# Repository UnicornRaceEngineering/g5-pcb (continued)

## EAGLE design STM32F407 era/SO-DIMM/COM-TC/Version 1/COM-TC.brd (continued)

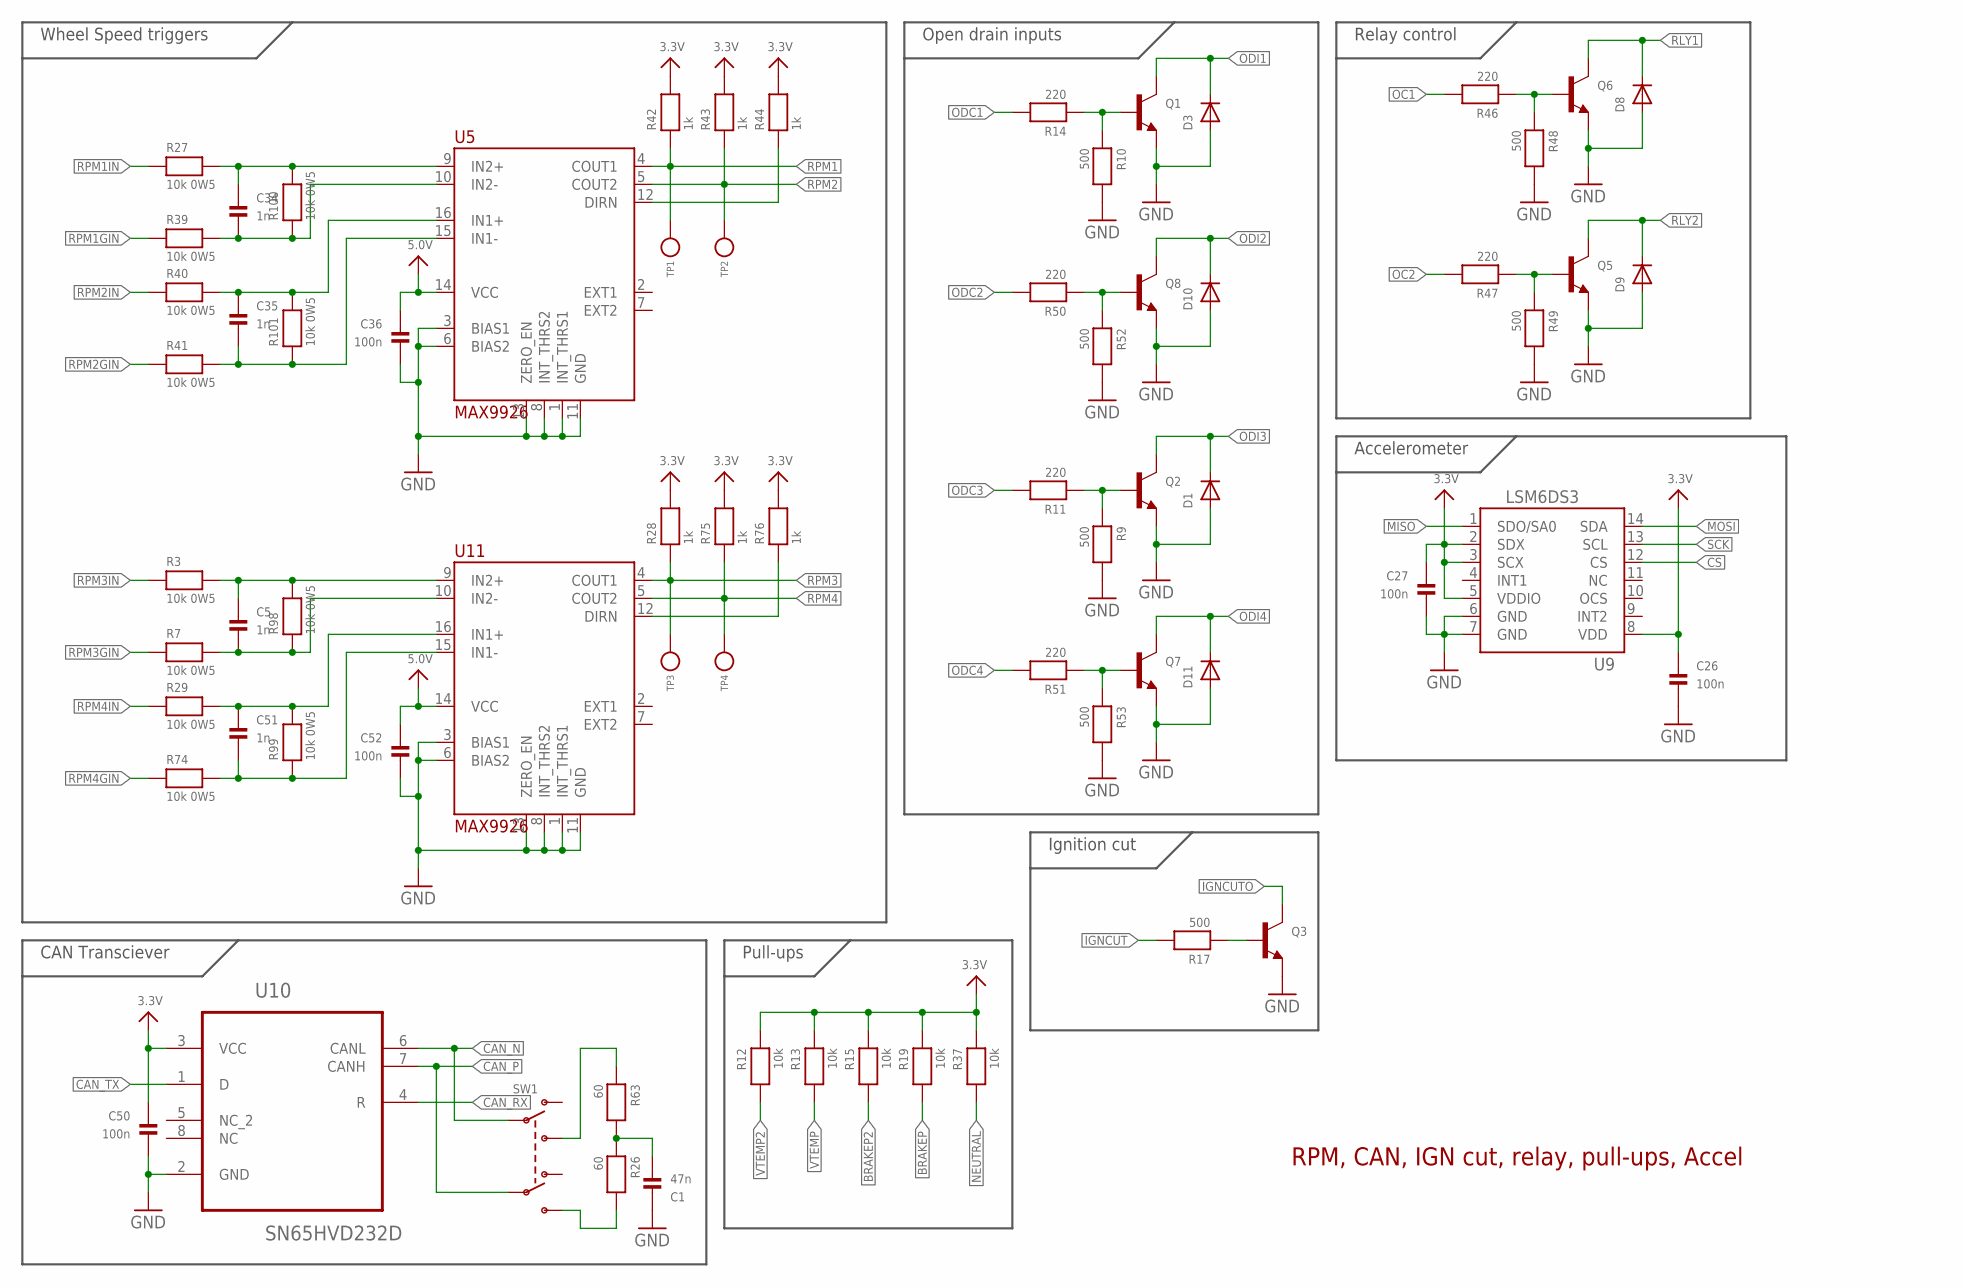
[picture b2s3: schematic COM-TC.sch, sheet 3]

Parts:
C1: 47n; _0603
C5, C34, C35, C51: 1n; _0603
C26, C27, C36, C50, C52: 100n; _0603
D1, D3, D8, D9, D10, D11: DIODESOD-323F; SOD-323F
Q1, Q2, Q3, Q5, Q6, Q7, Q8: TRANSISTOR_NPNWIDE; SOT23-WIDE
R3, R7, R27, R29, R39, R40, R41, R74, R98, R99, R100, R101: 10k 0W5; _0805
R9, R10, R17, R48, R49, R52, R53: 500; _0603
R11, R14, R46, R47, R50, R51: 220; _0603
R12, R13, R15, R19, R37: 10k; _0603
R26, R63: 60; _0603
R28, R42, R43, R44, R75, R76: 1k; _0603
SW1: SWITCH_DPDT; DPDT_SMT_JS202011SCQN
TP1, TP2, TP3, TP4: TEST_POINT_0.040IN; TESTPOINT_0.040IN
U5, U11: MAX9926; SOP63P600X175-16N
U9: LSM6DS3; LGA14L_DOT_INDICATOR
U10: SN65HVD232D; SOIC127P600X175-8N

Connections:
3.3V: C26.1, C27.1, C50.1, R12.1, R13.1, R15.1, R19.1, R28.2, R37.1, R42.2, R43.2, R44.2, R75.2, R76.2, U9.2 (SDX), U9.3 (SCX), U9.5 (VDDIO), U9.8 (VDD), U10.3 (VCC); also elsewhere on the board
5.0V: C36.1, C52.1, U5.14 (VCC), U11.14 (VCC); also elsewhere on the board
BRAKEP: R19.2; also elsewhere on the board
BRAKEP2: R15.2; also elsewhere on the board
CAN_N: SW1.P$2 (P1), U10.6 (CANL); also elsewhere on the board
CAN_P: SW1.P$5 (P2), U10.7 (CANH); also elsewhere on the board
CAN_RX: U10.4 (R); also elsewhere on the board
CAN_TX: U10.1 (D); also elsewhere on the board
CS: U9.12 (CS); also elsewhere on the board
GND: C1.1, C26.2, C27.2, C36.2, C50.2, C52.2, D1.A, D3.A, D8.A, D9.A, D10.A, D11.A, Q1.2 (E), Q2.2 (E), Q3.2 (E), Q5.2 (E), Q6.2 (E), Q7.2 (E), Q8.2 (E), R9.2, R10.2, R48.2, R49.2, R52.2, R53.2, U5.1 (INT_THRS1), U5.3 (BIAS1), U5.6 (BIAS2), U5.8 (INT_THRS2), U5.11 (GND), U5.13 (ZERO_EN), U9.6 (GND), U9.7 (GND), U10.2 (GND), U11.1 (INT_THRS1), U11.3 (BIAS1), U11.6 (BIAS2), U11.8 (INT_THRS2), U11.11 (GND), U11.13 (ZERO_EN); also elsewhere on the board
IGNCUT: R17.2; also elsewhere on the board
IGNCUTO: Q3.3 (C); also elsewhere on the board
MISO: U9.1 (SDO/SA0); also elsewhere on the board
MOSI: U9.14 (SDA); also elsewhere on the board
unnamed: R63.1, SW1.P$3 (S1)
unnamed: Q2.1 (B), R9.1, R11.1
unnamed: C1.2, R26.1, R63.2
unnamed: Q6.1 (B), R46.1, R48.1
unnamed: Q1.1 (B), R10.1, R14.1
unnamed: C34.1, R27.2, R100.2, U5.9 (IN2+)
unnamed: Q5.1 (B), R47.1, R49.1
unnamed: C35.2, R41.2, R101.1, U5.15 (IN1-)
unnamed: C5.1, R3.2, R98.2, U11.9 (IN2+)
unnamed: C35.1, R40.2, R101.2, U5.16 (IN1+)
unnamed: C34.2, R39.2, R100.1, U5.10 (IN2-)
unnamed: C51.2, R74.2, R99.1, U11.15 (IN1-)
unnamed: Q8.1 (B), R50.1, R52.1
unnamed: Q7.1 (B), R51.1, R53.1
unnamed: Q3.1 (B), R17.1
unnamed: C51.1, R29.2, R99.2, U11.16 (IN1+)
unnamed: C5.2, R7.2, R98.1, U11.10 (IN2-)
unnamed: R44.1, U5.12 (DIRN)
unnamed: R26.2, SW1.P$4 (S2)
unnamed: R76.1, U11.12 (DIRN)
NEUTRAL: R37.2; also elsewhere on the board
OC1: R46.2; also elsewhere on the board
OC2: R47.2; also elsewhere on the board
ODC1: R14.2; also elsewhere on the board
ODC2: R50.2; also elsewhere on the board
ODC3: R11.2; also elsewhere on the board
ODC4: R51.2; also elsewhere on the board
ODI1: D3.C, Q1.3 (C); also elsewhere on the board
ODI2: D10.C, Q8.3 (C); also elsewhere on the board
ODI3: D1.C, Q2.3 (C); also elsewhere on the board
ODI4: D11.C, Q7.3 (C); also elsewhere on the board
RLY1: D8.C, Q6.3 (C); also elsewhere on the board
RLY2: D9.C, Q5.3 (C); also elsewhere on the board
RPM1: R42.1, TP1.TESTPOINT, U5.4 (COUT1); also elsewhere on the board
RPM1GIN: R39.1; also elsewhere on the board
RPM1IN: R27.1; also elsewhere on the board
RPM2: R43.1, TP2.TESTPOINT, U5.5 (COUT2); also elsewhere on the board
RPM2GIN: R41.1; also elsewhere on the board
RPM2IN: R40.1; also elsewhere on the board
RPM3: R28.1, TP3.TESTPOINT, U11.4 (COUT1); also elsewhere on the board
RPM3GIN: R7.1; also elsewhere on the board
RPM3IN: R3.1; also elsewhere on the board
RPM4: R75.1, TP4.TESTPOINT, U11.5 (COUT2); also elsewhere on the board
RPM4GIN: R74.1; also elsewhere on the board
RPM4IN: R29.1; also elsewhere on the board
SCK: U9.13 (SCL); also elsewhere on the board
VTEMP: R13.2; also elsewhere on the board
VTEMP2: R12.2; also elsewhere on the board

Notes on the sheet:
CAN Transciever
Ignition cut
Wheel Speed triggers
Relay control
Open drain inputs
Pull-ups
Accelerometer
RPM, CAN, IGN cut, relay, pull-ups, Accel

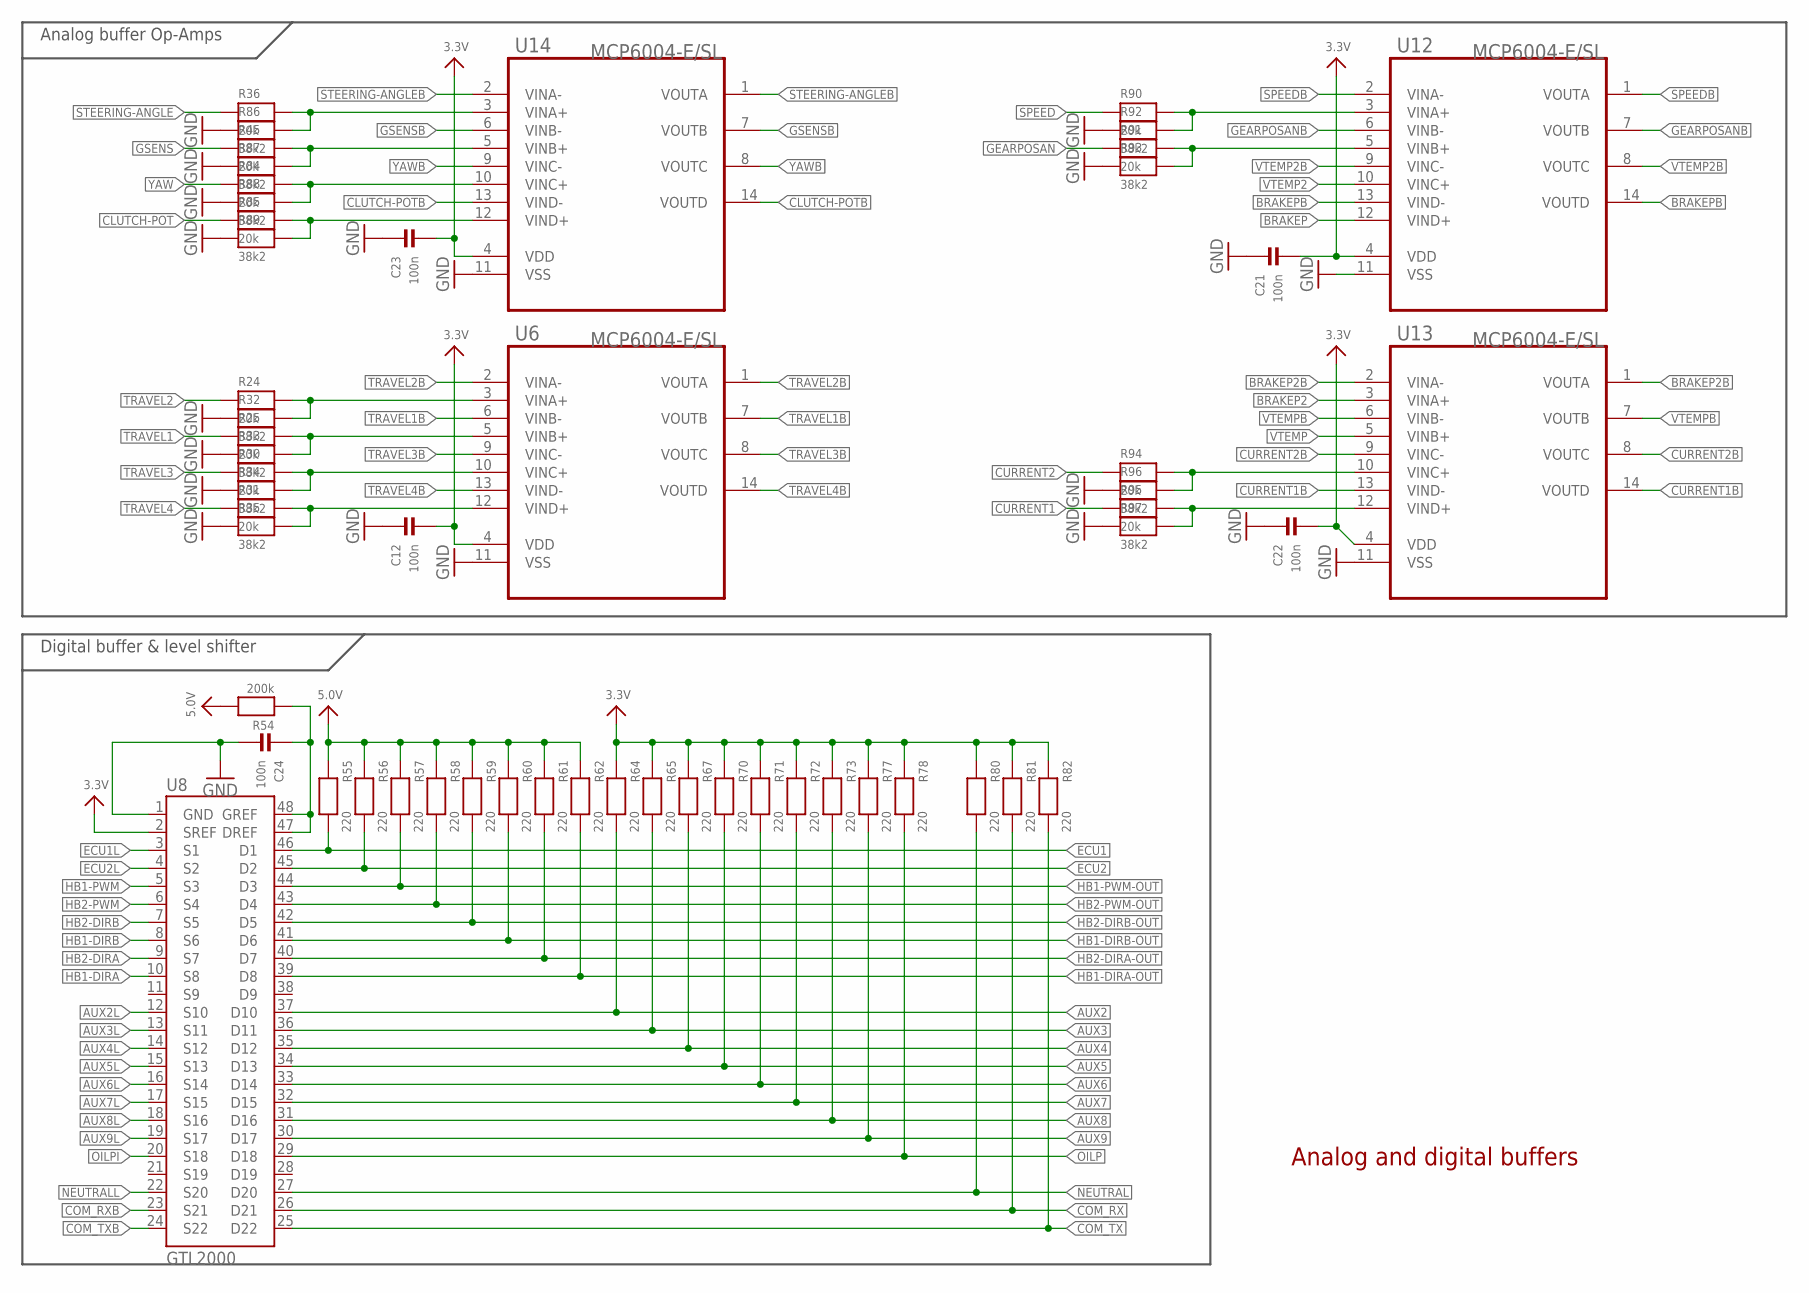
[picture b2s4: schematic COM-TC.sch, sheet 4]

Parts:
C12, C21, C22, C23, C24: 100n; _0603
R24, R25, R30, R31, R36, R45, R84, R85, R90, R91, R94, R95: 20k; _0603
R32, R33, R34, R35, R86, R87, R88, R89, R92, R93, R96, R97: 38k2; _0603
R54: 200k; _0603
R55, R56, R57, R58, R59, R60, R61, R62, R64, R65, R67, R70, R71, R72, R73, R77, R78, R80, R81, R82: 220; _0603
U6, U12, U13, U14: MCP6004-E/SL; SOIC127P600X175-14N
U8: GTL2000; TSSOP48

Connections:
3.3V: C12.2, C21.2, C22.2, C23.2, R64.1, R65.1, R67.1, R70.1, R71.1, R72.1, R73.1, R77.1, R78.1, R80.1, R81.1, R82.1, U6.4 (VDD), U8.2 (SREF), U12.4 (VDD), U13.4 (VDD), U14.4 (VDD); also elsewhere on the board
5.0V: R54.2, R55.1, R56.1, R57.1, R58.1, R59.1, R60.1, R61.1, R62.1; also elsewhere on the board
AUX2: R64.2, U8.37 (D10); also elsewhere on the board
AUX2L: U8.12 (S10); also elsewhere on the board
AUX3: R65.2, U8.36 (D11); also elsewhere on the board
AUX3L: U8.13 (S11); also elsewhere on the board
AUX4: R67.2, U8.35 (D12); also elsewhere on the board
AUX4L: U8.14 (S12); also elsewhere on the board
AUX5: R70.2, U8.34 (D13); also elsewhere on the board
AUX5L: U8.15 (S13); also elsewhere on the board
AUX6: R71.2, U8.33 (D14); also elsewhere on the board
AUX6L: U8.16 (S14); also elsewhere on the board
AUX7: R72.2, U8.32 (D15); also elsewhere on the board
AUX7L: U8.17 (S15); also elsewhere on the board
AUX8: R73.2, U8.31 (D16); also elsewhere on the board
AUX8L: U8.18 (S16); also elsewhere on the board
AUX9: R77.2, U8.30 (D17); also elsewhere on the board
AUX9L: U8.19 (S17); also elsewhere on the board
BRAKEP: U12.12 (VIND+); also elsewhere on the board
BRAKEP2: U13.3 (VINA+); also elsewhere on the board
BRAKEP2B: U13.1 (VOUTA), U13.2 (VINA-); also elsewhere on the board
BRAKEPB: U12.13 (VIND-), U12.14 (VOUTD); also elsewhere on the board
CLUTCH-POT: R85.1; also elsewhere on the board
CLUTCH-POT1: R31.2, R35.2, U6.12 (VIND+)
CLUTCH-POTB: U14.13 (VIND-), U14.14 (VOUTD); also elsewhere on the board
COM_RX: R81.2, U8.26 (D21); also elsewhere on the board
COM_RXB: U8.23 (S21); also elsewhere on the board
COM_TX: R82.2, U8.25 (D22); also elsewhere on the board
COM_TXB: U8.24 (S22); also elsewhere on the board
CURRENT1: R95.1; also elsewhere on the board
CURRENT1B: U13.13 (VIND-), U13.14 (VOUTD); also elsewhere on the board
CURRENT2: R94.1; also elsewhere on the board
CURRENT2B: U13.8 (VOUTC), U13.9 (VINC-); also elsewhere on the board
ECU1: R55.2, U8.46 (D1); also elsewhere on the board
ECU1L: U8.3 (S1); also elsewhere on the board
ECU2: R56.2, U8.45 (D2); also elsewhere on the board
ECU2L: U8.4 (S2); also elsewhere on the board
GEARPOSAN: R91.1; also elsewhere on the board
GEARPOSANB: U12.6 (VINB-), U12.7 (VOUTB); also elsewhere on the board
GND: C12.1, C21.1, C22.1, C23.1, C24.2, R32.1, R33.1, R34.1, R35.1, R86.1, R87.1, R88.1, R89.1, R92.1, R93.1, R96.1, R97.1, U6.11 (VSS), U8.1 (GND), U12.11 (VSS), U13.11 (VSS), U14.11 (VSS); also elsewhere on the board
GSENS: R45.1; also elsewhere on the board
GSENSB: U14.6 (VINB-), U14.7 (VOUTB); also elsewhere on the board
GSENSL1: R25.2, R33.2, U6.5 (VINB+)
GSENSL2: R91.2, R93.2, U12.5 (VINB+)
GSENSL3: R95.2, R97.2, U13.12 (VIND+)
HB1-DIRA: U8.10 (S8); also elsewhere on the board
HB1-DIRA-OUT: R62.2, U8.39 (D8); also elsewhere on the board
HB1-DIRB: U8.8 (S6); also elsewhere on the board
HB1-DIRB-OUT: R60.2, U8.41 (D6); also elsewhere on the board
HB1-PWM: U8.5 (S3); also elsewhere on the board
HB1-PWM-OUT: R57.2, U8.44 (D3); also elsewhere on the board
HB2-DIRA: U8.9 (S7); also elsewhere on the board
HB2-DIRA-OUT: R61.2, U8.40 (D7); also elsewhere on the board
HB2-DIRB: U8.7 (S5); also elsewhere on the board
HB2-DIRB-OUT: R59.2, U8.42 (D5); also elsewhere on the board
HB2-PWM: U8.6 (S4); also elsewhere on the board
HB2-PWM-OUT: R58.2, U8.43 (D4); also elsewhere on the board
unnamed: R85.2, R89.2, U14.12 (VIND+)
unnamed: C24.1, R54.1, U8.47 (DREF), U8.48 (GREF)
unnamed: R84.2, R88.2, U14.10 (VINC+)
unnamed: R45.2, R87.2, U14.5 (VINB+)
unnamed: R36.2, R86.2, U14.3 (VINA+)
NEUTRAL: R80.2, U8.27 (D20); also elsewhere on the board
NEUTRALL: U8.22 (S20); also elsewhere on the board
OILP: R78.2, U8.29 (D18); also elsewhere on the board
OILPI: U8.20 (S18); also elsewhere on the board
SPEED: R90.1; also elsewhere on the board
SPEEDB: U12.1 (VOUTA), U12.2 (VINA-); also elsewhere on the board
STEERING-ANGLE: R36.1; also elsewhere on the board
STEERING-ANGLE1: R24.2, R32.2, U6.3 (VINA+)
STEERING-ANGLE2: R90.2, R92.2, U12.3 (VINA+)
STEERING-ANGLE3: R94.2, R96.2, U13.10 (VINC+)
STEERING-ANGLEB: U14.1 (VOUTA), U14.2 (VINA-); also elsewhere on the board
TRAVEL1: R25.1; also elsewhere on the board
TRAVEL1B: U6.6 (VINB-), U6.7 (VOUTB); also elsewhere on the board
TRAVEL2: R24.1; also elsewhere on the board
TRAVEL2B: U6.1 (VOUTA), U6.2 (VINA-); also elsewhere on the board
TRAVEL3: R30.1; also elsewhere on the board
TRAVEL3B: U6.8 (VOUTC), U6.9 (VINC-); also elsewhere on the board
TRAVEL4: R31.1; also elsewhere on the board
TRAVEL4B: U6.13 (VIND-), U6.14 (VOUTD); also elsewhere on the board
VTEMP: U13.5 (VINB+); also elsewhere on the board
VTEMP2: U12.10 (VINC+); also elsewhere on the board
VTEMP2B: U12.8 (VOUTC), U12.9 (VINC-); also elsewhere on the board
VTEMPB: U13.6 (VINB-), U13.7 (VOUTB); also elsewhere on the board
YAW: R84.1; also elsewhere on the board
YAWB: U14.8 (VOUTC), U14.9 (VINC-); also elsewhere on the board
YAWL1: R30.2, R34.2, U6.10 (VINC+)

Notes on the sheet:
Digital buffer & level shifter
Analog buffer Op-Amps
Analog and digital buffers

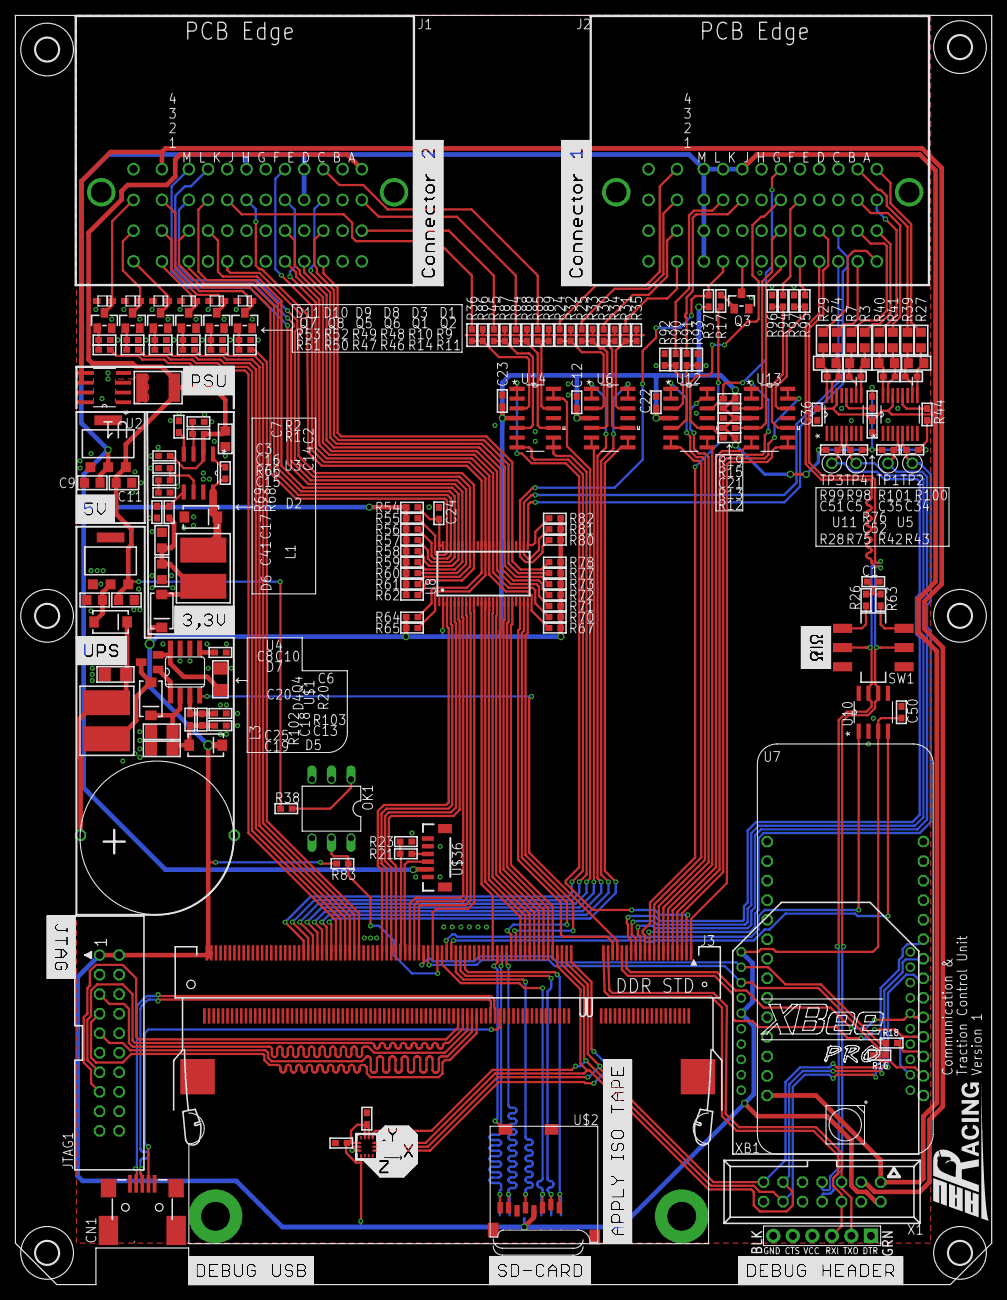
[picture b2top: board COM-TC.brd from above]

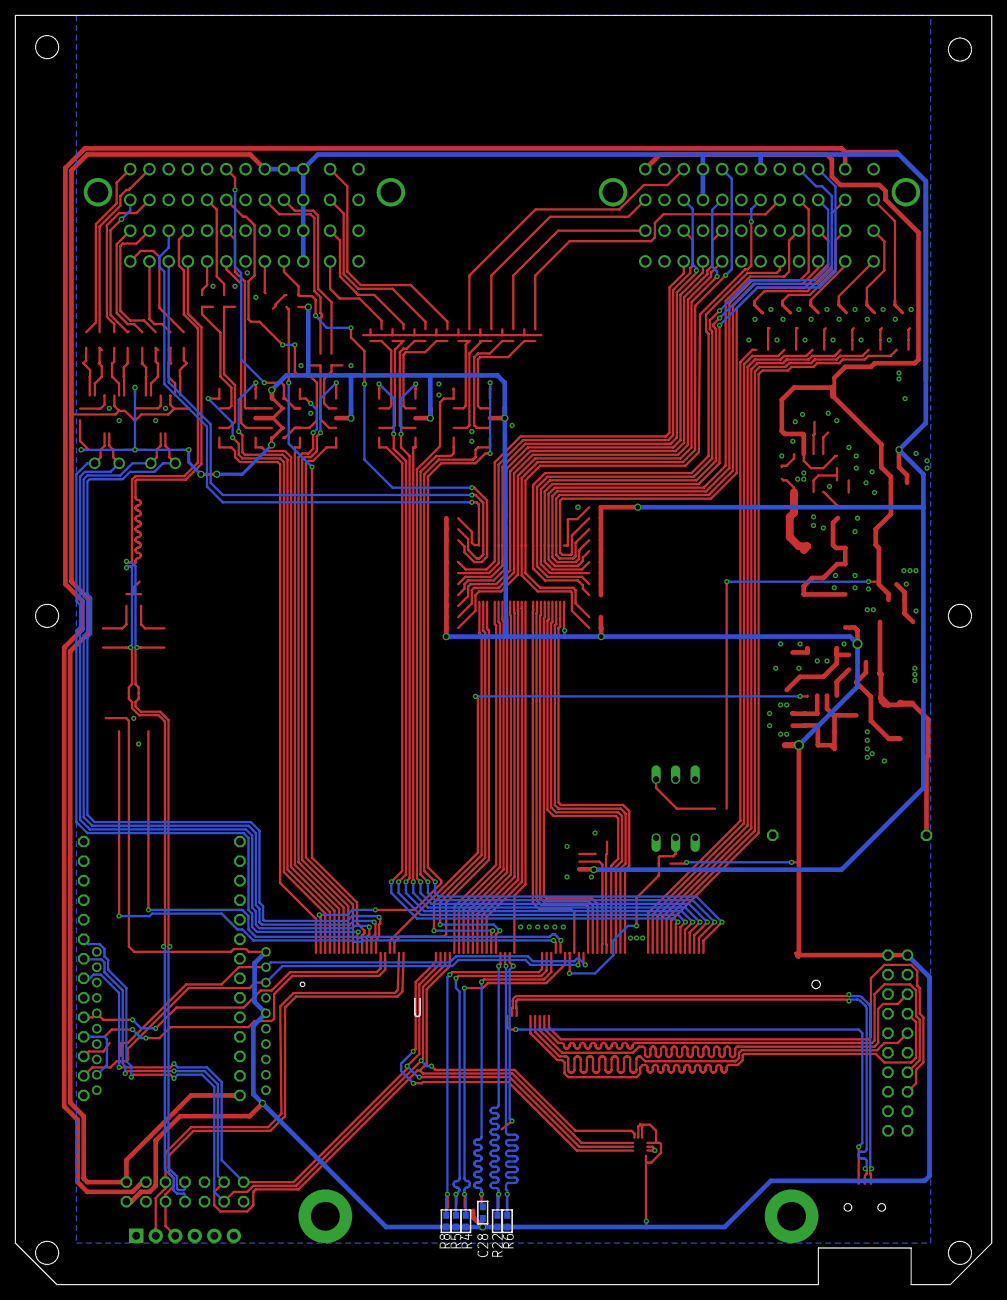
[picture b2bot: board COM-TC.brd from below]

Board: 2 copper layers, 127.0 x 165.1 mm, 196 parts (6 on the bottom side), 189 nets.
